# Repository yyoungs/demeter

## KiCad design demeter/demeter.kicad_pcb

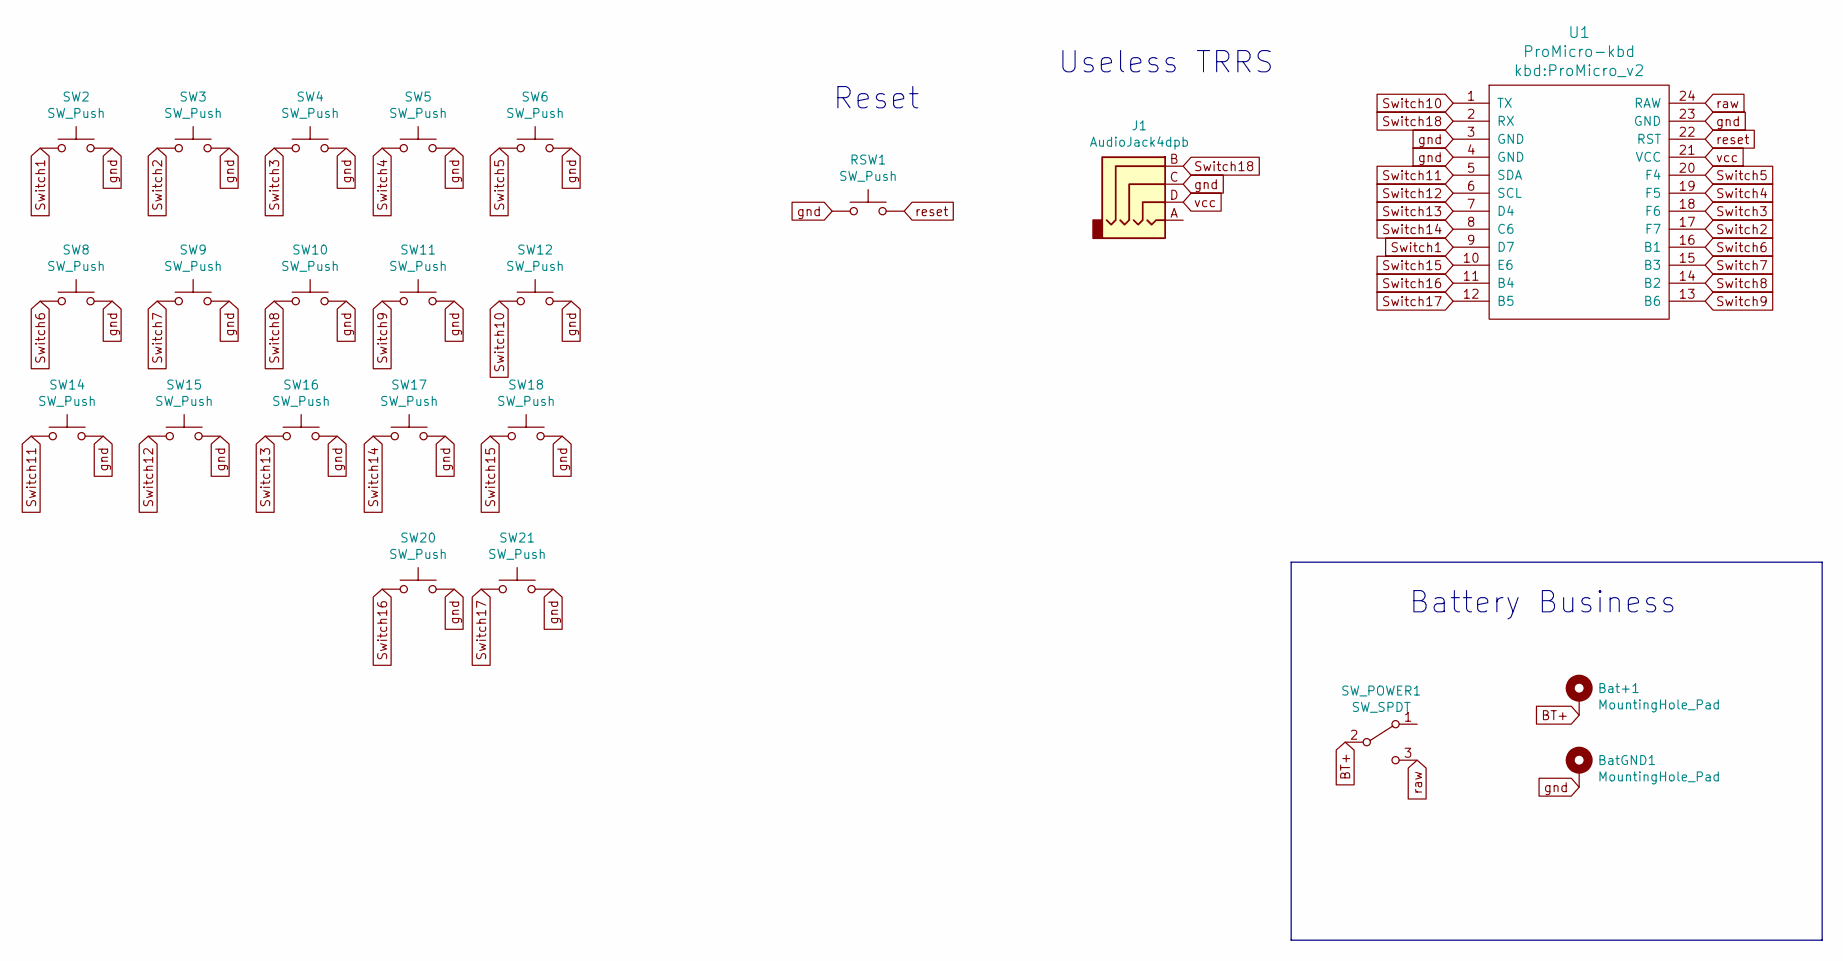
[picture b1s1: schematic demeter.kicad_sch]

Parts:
Bat+1: MountingHole_Pad; 1pin_conn
BatGND1: MountingHole_Pad; 1pin_conn
J1: AudioJack4dpb; MJ-4PP-9
RSW1: SW_Push; ResetSW
SW2, SW3, SW4, SW5, SW6, SW8, SW9, SW10, SW11, SW12, SW14, SW15, SW16, SW17, SW18, SW20, SW21: SW_Push; SW_PG1350_rev_DPB
SW_POWER1: SW_SPDT; SPDT_C128955
U1: ProMicro-kbd; ProMicro_v2

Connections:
BT+: Bat+1.1, SW_POWER1.2 (B), U1.27; also elsewhere on the board
Switch1: SW2.1, U1.9 (D7)
Switch2: SW3.1, U1.17 (F7)
Switch3: SW4.1, U1.18 (F6)
Switch4: SW5.1, U1.19 (F5)
Switch5: SW6.1, U1.20 (F4)
Switch6: SW8.1, U1.16 (B1)
Switch7: SW9.1, U1.15 (B3)
Switch8: SW10.1, U1.14 (B2)
Switch9: SW11.1, U1.13 (B6)
Switch10: SW12.1, U1.1 (TX)
Switch11: SW14.1, U1.5 (SDA)
Switch12: SW15.1, U1.6 (SCL)
Switch13: SW16.1, U1.7 (D4)
Switch14: SW17.1, U1.8 (C6)
Switch15: SW18.1, U1.10 (E6)
Switch16: SW20.1, U1.11 (B4)
Switch17: SW21.1, U1.12 (B5)
Switch18: J1.B, U1.2 (RX)
gnd: BatGND1.1, J1.C, RSW1.1, SW2.2, SW3.2, SW4.2, SW5.2, SW6.2, SW8.2, SW9.2, SW10.2, SW11.2, SW12.2, SW14.2, SW15.2, SW16.2, SW17.2, SW18.2, SW20.2, SW21.2, U1.3 (GND), U1.4 (GND), U1.23 (GND)
raw: SW_POWER1.3 (C), U1.24 (RAW); also elsewhere on the board
reset: RSW1.2, U1.22 (RST)
vcc: J1.D, U1.21 (VCC)

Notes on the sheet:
Reset
Battery Business
Useless TRRS

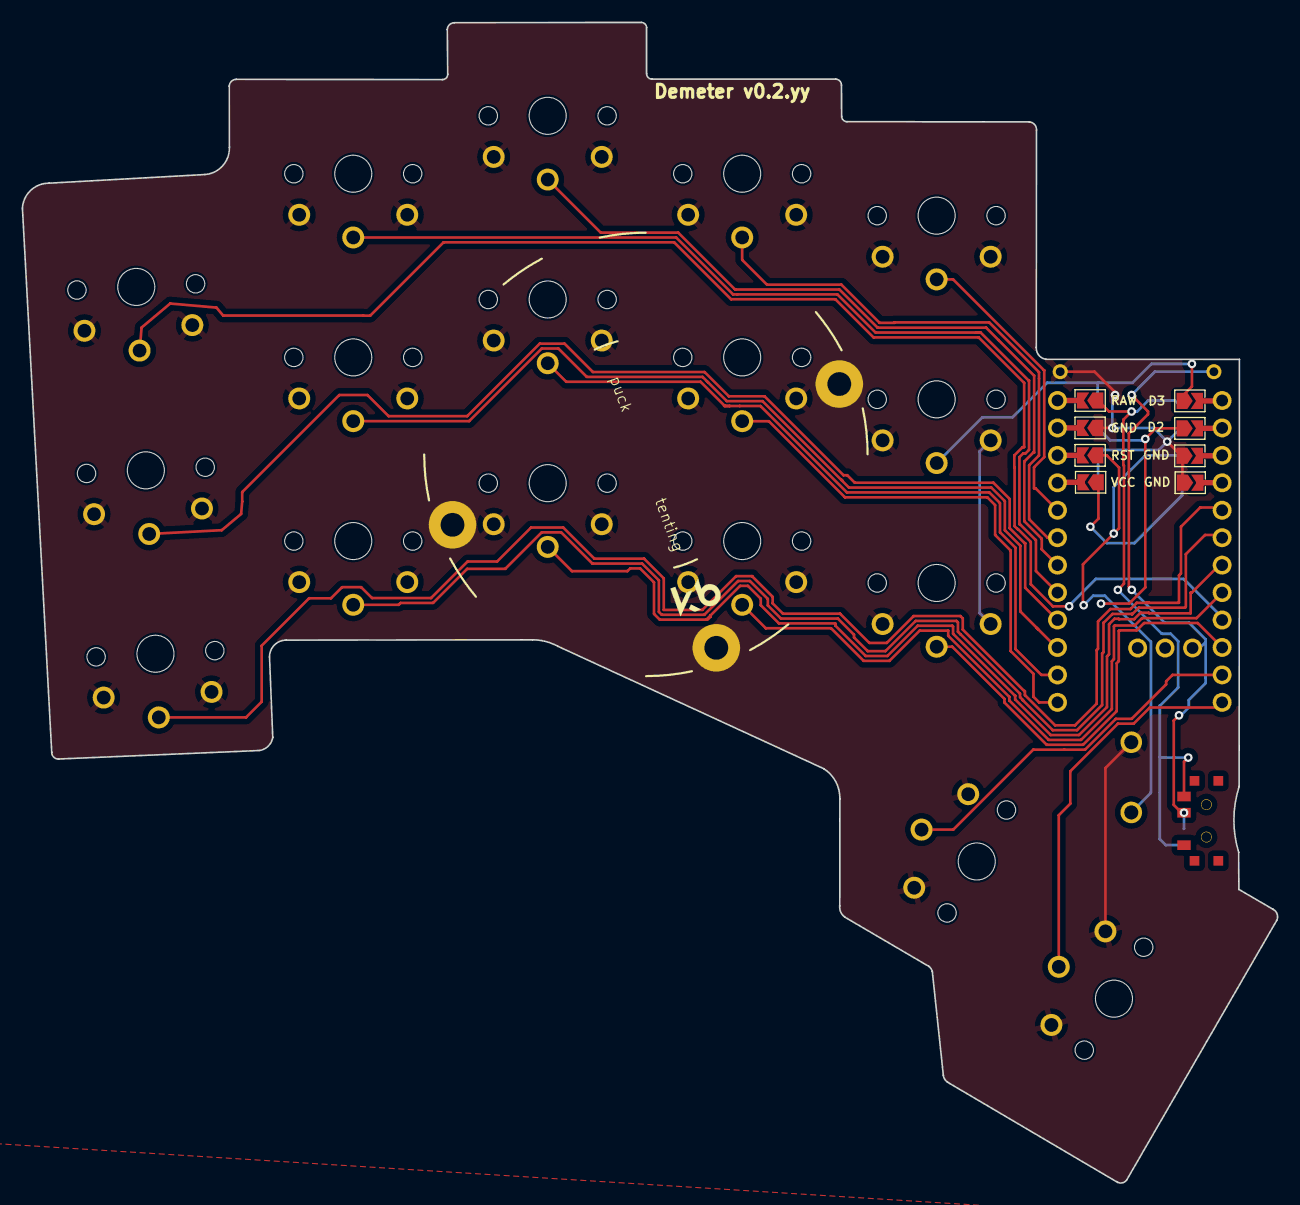
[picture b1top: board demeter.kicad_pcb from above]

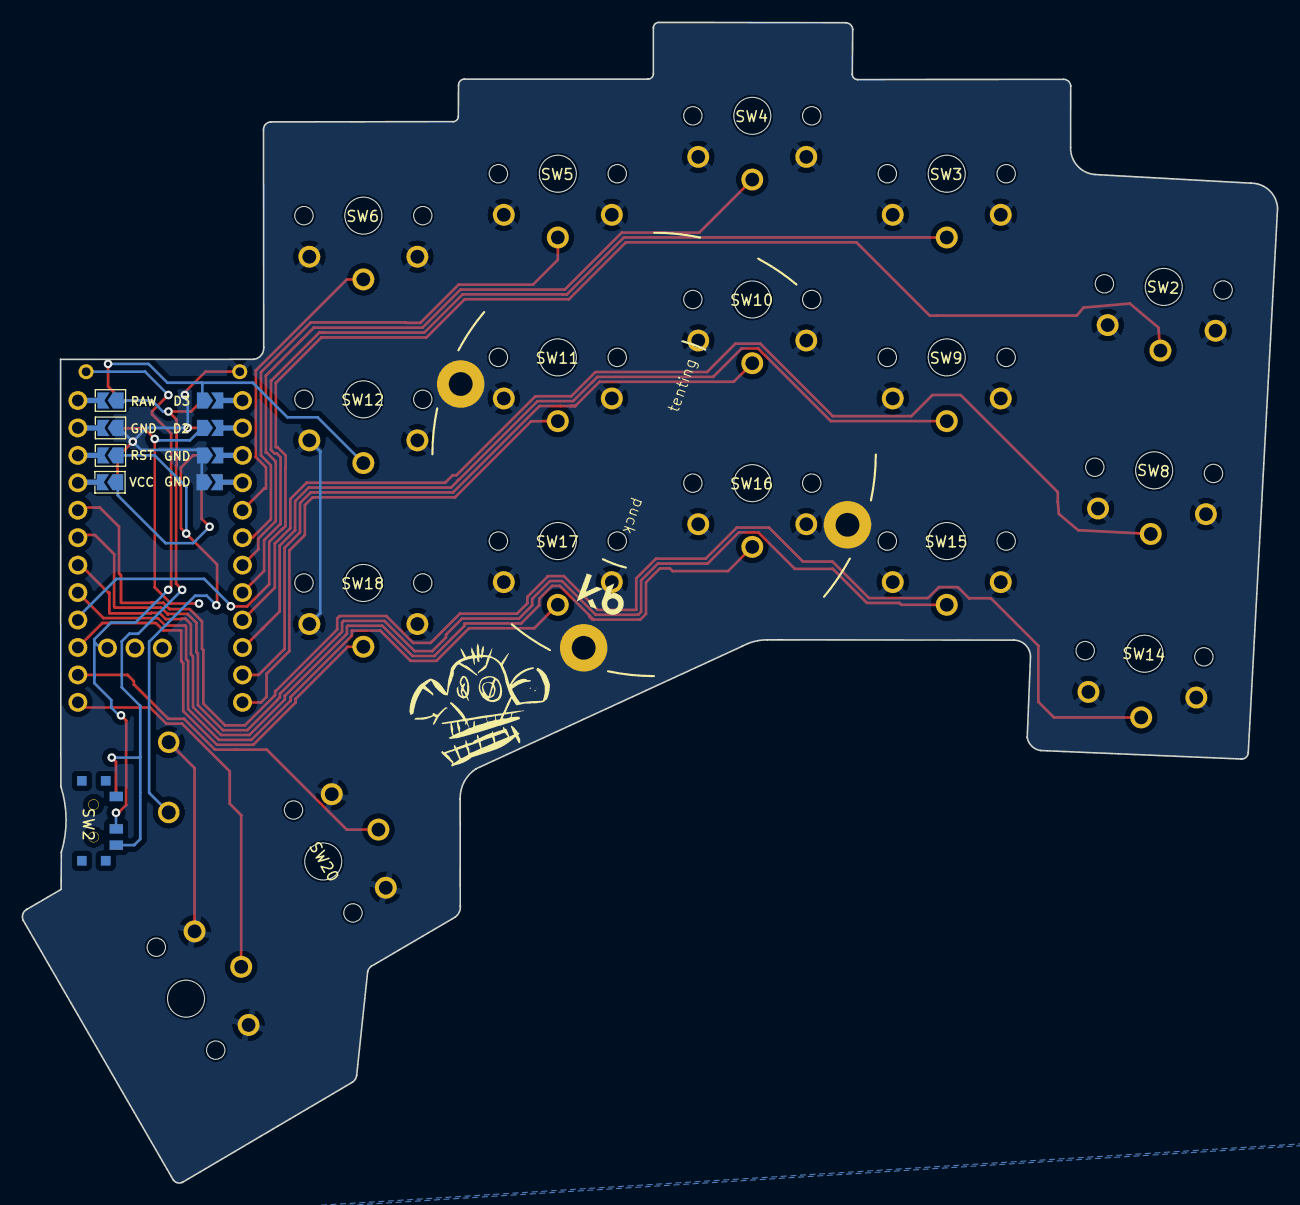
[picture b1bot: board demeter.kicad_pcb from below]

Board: 2 copper layers, 116.2 x 107.4 mm, 23 parts (2 on the bottom side), 21 nets.

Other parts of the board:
SW2#2: SW_SPDT; SPDT_C128955r

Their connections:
BT+: SW2#2.2; also elsewhere on the board
raw: SW2#2.3; also elsewhere on the board

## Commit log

2025-12-28 clone wireless dir
2025-12-28 migrate to kicad v9
2025-12-28 update legend
2025-12-28 add modified tenting puck footprint
2025-12-28 add monkey image
2025-12-30 add gerbers
2026-05-25 wip: unknown last changes
